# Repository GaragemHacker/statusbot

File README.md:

# statusbot
Clever Joke Bot to make the Garage more acessible in the web

### Task's (to-do's)

 * Python Chatter Bot on IRC
 * HackerSpace Door status
 * ~~Yowsup intergation~~
 * Telegram @ElviraBot(raimundod.py)
 * WebSite and Wiki hackerspace status

### status.php

Para passar o status do hackerspace como aberto, foi optado por usar o status.php que grava um arquivo status.txt com o estado do hackerspace. A requisicao e feito por um arduino com ethernet shield.

-------

### statusbot(turnkey/push).ino

Statusbot task's com Arduino
 - [x] Receber DHCP
 - [x] Imprimir tudo que estiver colhendo em Serial
 - [x] Aceitar requisicoes ping
 - [x] Fazer UrlRequest <i>(quando o estado se alterar)</i>
 - [ ] Twittar Status

Estou deixando para estudo de caso duas versões diferentes para arduino.
A versao <i>"turnkey"</i> usa a interrupcao como leitura e pode ser usado com botoes tradicionais tipo switch. O arquivo statusbot_push.ino tem um algoritimo que ira funcionar com botoes <i>"push"</i>. 

#### Exemplos de botoes
  | 
------------- | -------------
<i>Switch Gangorra</i>  | <i>Push button</i>

-------

### ircbot.py

Chatter bot, para notificao de status com WhatsApp e IRC
 * Notificao de presenca no HackerSpace pelo IRC
 * Aviso da abertura para WhatsApp com integracao ao yowsup
 * Auto voices novos visitantes do canal
 * Vocabulario atrevido de respostas

-------

### lamp.js/lamp.php (<i>lamp_sample.html</i>)
Pequeno exemplo de como usar a API para colher o estado da garagem.
O exemplo que usa um javascript colhe o estado do arquivo status.txt e quando aberto mostra uma lampada acesa no html. Quando apagado mostra uma lampada apagada.
O que esta php faz exatamente a mesma coisa em php :stuck_out_tongue:

<br>
<i>Lampada usada no site da <a href="http://www.garagemhacker.org">garagemhacker</a></i>

-------

### raiumundod.py

O raimundo tambem conhecido como @RaimundaBot, e o bot atual do telegram da Garagem. 
Este bot deve fazer as seguintes funcoes:

 - [x] Verificar o status da garagem se esta aberta o fechada "/status"
 - [ ] Ecoar as conversar do telegram no canal do irc
 - [ ] Mostrar quem esta na garagem pelo comando "/quemtala" 
 - [ ] Dizer algumas frases legais quando for mencionado 

-------

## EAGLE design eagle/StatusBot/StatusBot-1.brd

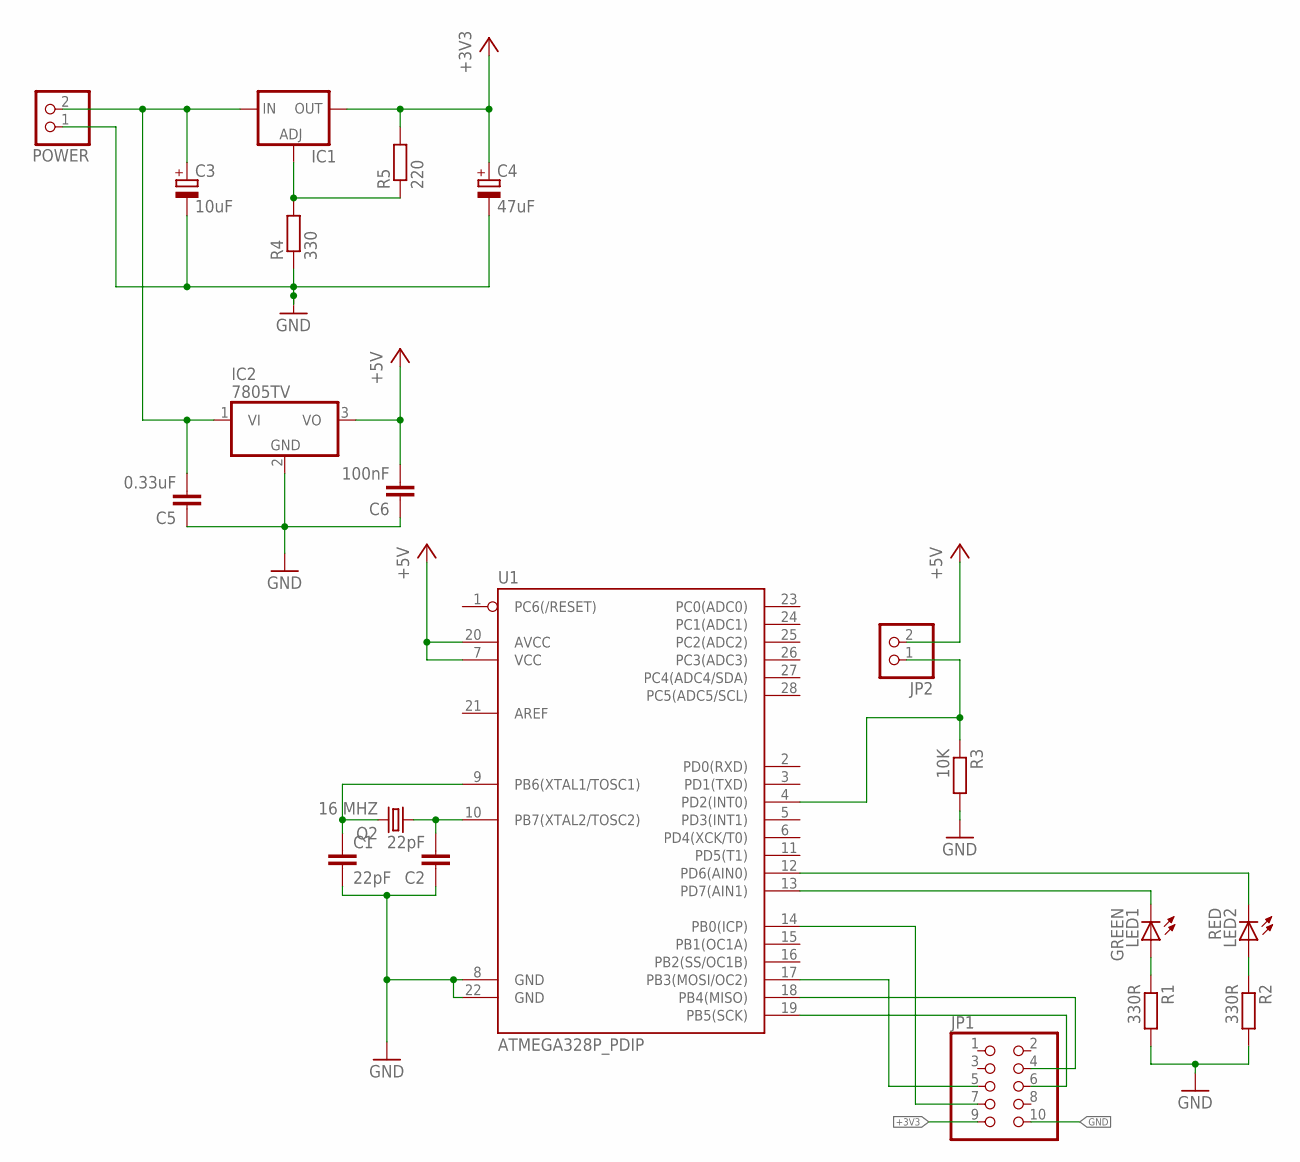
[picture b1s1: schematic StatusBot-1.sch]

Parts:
C1, C2: 22pF; C025-024X044
C3: 10uF; E3,5-8
C4: 47uF; E3,5-8
C5: 0.33uF; C025-024X044
C6: 100nF; C025-024X044
IC1: LM317TS; 317TS
IC2: 7805TV; TO220V
JP1: PINHD-2X5; 2X05
JP2: PINHD-1X2; 1X02
LED1: GREEN; LED5MM
LED2: RED; LED5MM
POWER: PINHD-1X2; 1X02
Q2: 16 MHZ; HC49/S
R1, R2: 330R; 0204/5
R3: 10K; 0204/5
R4: 330; 0207/10
R5: 220; 0207/10
U1: ATMEGA328P_PDIP; DIL28-3

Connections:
+3V3: C4.+, IC1.2 (OUT), JP1.9, R5.2
+5V: C6.2, IC2.3 (VO), JP2.2, U1.7 (VCC), U1.20 (AVCC)
GND: C1.2, C2.1, C3.-, C4.-, C5.1, C6.1, IC2.2 (GND), JP1.10, POWER.1, R1.2, R2.2, R3.2, R4.1, U1.8 (GND), U1.22 (GND)
unnamed: C2.2, Q2.1, U1.10 (PB7(XTAL2/TOSC2))
unnamed: JP1.7, U1.14 (PB0(ICP))
unnamed: JP2.1, R3.1, U1.4 (PD2(INT0))
unnamed: C1.1, Q2.2, U1.9 (PB6(XTAL1/TOSC1))
unnamed: C3.+, C5.2, IC1.3 (IN), IC2.1 (VI), POWER.2
unnamed: LED1.A, R1.1
unnamed: LED2.A, R2.1
unnamed: JP1.5, U1.17 (PB3(MOSI/OC2))
unnamed: LED2.K (C), U1.12 (PD6(AIN0))
unnamed: LED1.K (C), U1.13 (PD7(AIN1))
unnamed: JP1.4, U1.18 (PB4(MISO))
unnamed: JP1.6, U1.19 (PB5(SCK))
unnamed: IC1.1 (ADJ), R4.2, R5.1

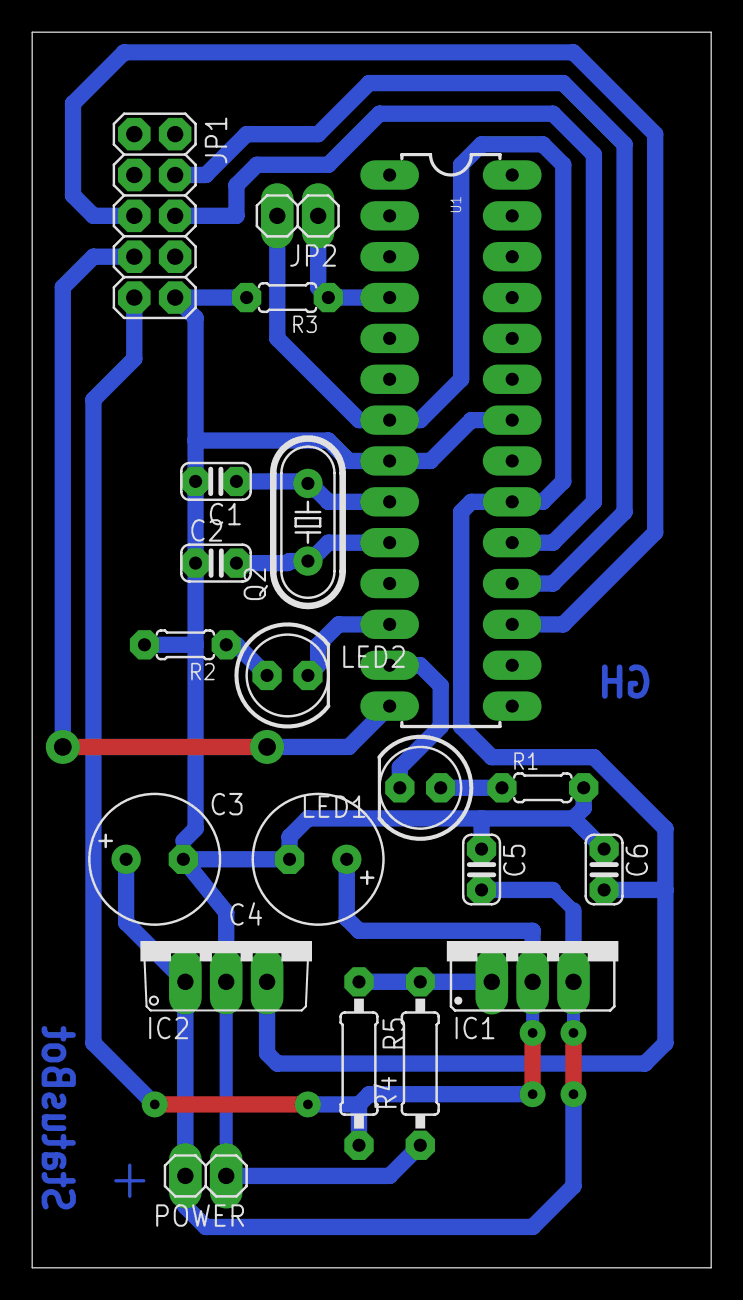
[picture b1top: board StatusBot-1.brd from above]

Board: 2 copper layers, 42.2 x 76.8 mm, 20 parts (0 on the bottom side), 16 nets.

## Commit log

2015-02-19 Update README.md
    Describe some features to be implemented
2015-02-28 Criacao do status.php
2015-03-04 Ino Bot
2015-03-04 Descricao de modificacoes
    novas modificacoes descriminadas
2015-03-04 Identention
    Melhoria na identacao
2015-03-04 statusbot com arduino
    Teste inicial do StatusBot
2015-03-06 Irc bot born
2015-03-07 Add IRQ button switch on Arduino StatusBot
2015-03-07 Add arduino integration Minor changes
2015-03-07 More description for ircbot
2015-03-07 PONG Reply to server
2015-03-08 ircbot now identifies to server
2015-03-11 Now the bot reconize you
2015-03-12 Add push and switch version
2015-03-12 Add little comments
    Add more comments for better explanation
2015-03-12 Add more readme help
    Better README.md description
2015-03-12 Add little comments
2015-03-14 Wordpress API
2015-03-14 Improve names for Arduino IDE
2015-03-14 Add wp_api description
2015-03-18 Split files to make a sample
2015-03-18 lamp.js fully working
2015-03-18 fully working, more debugs
2015-03-19 fully works
2015-03-20 better js explain, por edited on VI
2015-03-20 better explanation
    Better explanation for how use status.txt API with js and html sample
2015-03-26 added split lamps
2015-03-26 fix split lamps sizes
2015-03-26 improve and simplified the image change
2015-03-27 sample python urllib
2015-03-27 New status function for ircbot
2015-03-27 Now the bot send channel state to the irc channel
2015-03-27 buggy nights uggy buggy
2015-03-27 Now can tell you the hackerspace status
2015-03-27 status only tell the state when ponging
2015-03-27 added twitter api
2015-03-28 Ino Fully works
2015-03-28 fix little bugs - stay fully working
2015-03-29 added geting HackerSpace status from php
2015-03-30 present the web samples
    Leia, entenda e use!!!
2015-03-31 ircbot now autovoice's new joiner's
2015-03-31 improve explain
2015-03-31 improve visual code
2015-04-01 lot improve on code style
2015-04-01 bot start to be more
2015-04-02 fix crash when socket failed
2015-04-08 trying to fix auto-reconnect bug
2015-04-08 improve the way bot dies
2015-04-19 fix the recconect issue
2015-04-23 Added timeout for socket when expires leasetime. It means, this bot now save last ping server time and compare it with current time if its exceed the leasetime variable value it try's to reconnect.
2015-04-23 Improve leasetime used for autoreconnect
2015-04-23 improve pings with leasetime
2015-04-23 improve killme function
2015-05-07 minor improvements for socket exception
2015-05-07 trash threading code
2015-05-07 trash all expira function
2015-07-01 Error when conected fail
2015-07-03 PCB Statusbot
2015-07-11 Minor Description for elvirabot
    Only supports for status on for telegram user with @ElviraBot
2015-08-16 Added Telegram Bot - Just for this time the bot are called @RaimundaBot nick Raimundo soon whill integer on EvliraBot - This Bot get uptades from the telegram json updates and if recive the /status c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
2015-08-21 More tests to fix telegram bot Another try
2015-08-21 added telegram bot description
2015-08-21 fix error during conection on telegram bot
2015-12-05 removed error_dhcp function
2016-01-22 Started new API to List all members who are on HackerSpace
2016-02-10 improve sample for faster 301

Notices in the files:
parts and their libraries:
SparkFun-DigitalIC: Licensing: Creative Commons ShareAlike 4.0 International - https://creativecommons.org/licenses/by-sa/4.0
